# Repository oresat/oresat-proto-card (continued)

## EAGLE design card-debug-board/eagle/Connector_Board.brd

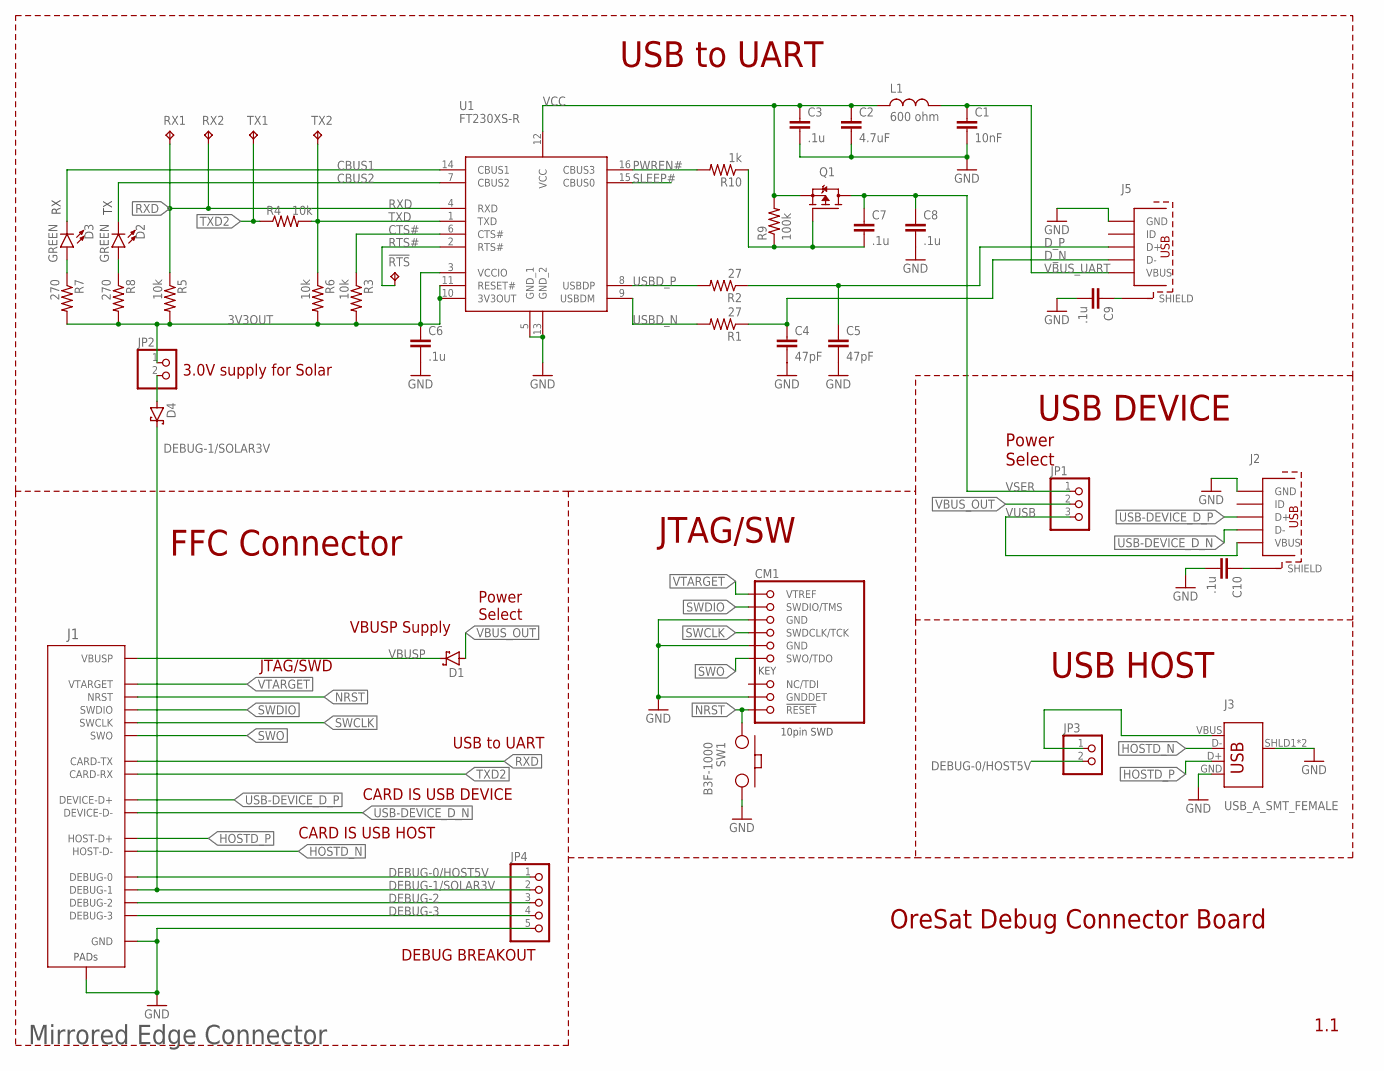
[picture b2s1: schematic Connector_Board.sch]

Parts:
!RTS: TEST-POINT-LARGE; 1X01
C1: 10nF; .0603-C-NOSILK; MANUFACTURER_PART_NUMBER 885382206002; DIGI-KEY_PART_NUMBER 732-13185-1-ND
C2: 4.7uF; .0603-C-NOSILK; MANUFACTURER_PART_NUMBER C1608X7S1A475K080AC; DIGI-KEY_PART_NUMBER 445-14258-1-ND
C3, C6, C7, C8, C9, C10: .1u; .0603-C-NOSILK; MANUFACTURER_PART_NUMBER 0603ZD104KAT2A; DIGI-KEY_PART_NUMBER 478-0603ZD104KAT2ACT-ND
C4, C5: 47pF; .0603-C-NOSILK; MANUFACTURER_PART_NUMBER 06033A470FAT2A; DIGI-KEY_PART_NUMBER 478-12679-1-ND
CM1: FTSH-105-XX-X-DV-K; CON10_2X5_DUK_FTSH; MANUFACTURER_PART_NUMBER FTSH-105-01-F-DV-K-TR; DIGI-KEY_PART_NUMBER SAM13160CT-ND
D1, D4: CDBU0520; DIOC1709X85N; MANUFACTURER_PART_NUMBER CDBU0520; DIGI-KEY_PART_NUMBER 641-1332-1-ND
D2, D3: GREEN; LED-0603; MANUFACTURER_PART_NUMBER 150060VS55040; DIGI-KEY_PART_NUMBER 732-12017-1-ND
J1: ORESAT-DEBUG-CONNECTOR-MIRRORED-ALL; TE_2-1734592-0; MANUFACTURER_PART_NUMBER 2-1734592-0; DIGI-KEY_PART_NUMBER A100287CT-ND
J2, J5: MICRO-USB-SOCKET; 629105136821; MANUFACTURER_PART_NUMBER 629105136821; DIGI-KEY_PART_NUMBER 732-3155-1-ND
J3: USB_A_SMT_FEMALE; USB-A-S-SILK-FEMALE; MANUFACTURER_PART_NUMBER PRT-09011; MOUSER_PART_NUMBER 474-PRT-09011
JP1: PINHD-1X3; 1X03; MANUFACTURER_PART_NUMBER 61300311121; DIGI-KEY_PART_NUMBER 732-5316-ND
JP2, JP3: PINHD-1X2; 1X02; MANUFACTURER_PART_NUMBER 61300211121; DIGI-KEY_PART_NUMBER 732-5315-ND
JP4: PINHD-1X5; 1X05; MANUFACTURER_PART_NUMBER 61300511121; DIGI-KEY_PART_NUMBER 732-5318-ND
L1: 600 ohm; .0805-A-NOSILK; MANUFACTURER_PART_NUMBER MI0805K601R-10; DIGI-KEY_PART_NUMBER 240-2390-1-ND
Q1: MOSFET-PCH-SOT23-6; SOT23-6; MANUFACTURER_PART_NUMBER SIL3407-TP; DIGI-KEY_PART_NUMBER SIL3407-TPMSCT-ND
R1, R2: 27; .0603-C-NOSILK; MANUFACTURER_PART_NUMBER CR0603-FX-27R0ELF; DIGI-KEY_PART_NUMBER CR0603-FX-27R0ELFCT-ND
R3, R4, R5, R6: 10k; .0603-C-NOSILK; MANUFACTURER_PART_NUMBER CR0603-FX-1002ELF; DIGI-KEY_PART_NUMBER CR0603-FX-1002ELFCT-ND
R7, R8: 270; .0603-C-NOSILK; MANUFACTURER_PART_NUMBER Panasonic Electronic Components; DIGI-KEY_PART_NUMBER P270HCT-ND
R9: 100k; .0603-C-NOSILK; MANUFACTURER_PART_NUMBER RMCF0603JG100K; DIGI-KEY_PART_NUMBER RMCF0603JG100KTR-ND
R10: 1k; .0603-C-NOSILK; MANUFACTURER_PART_NUMBER RC0603FR-071KL; DIGI-KEY_PART_NUMBER 311-1.00KHRCT-ND
RX1, RX2: TEST-POINT-LARGE; 1X01
SW1: B3F-1000; SW-MOM-OMRON-6X6X4.3; MANUFACTURER_PART_NUMBER B3F-1000; DIGI-KEY_PART_NUMBER SW400-ND
TX1, TX2: TEST-POINT-LARGE; 1X01
U1: FT230XS-R; SOP64P599X175-16N; DIGI-KEY_PART_NUMBER 768-1135-1-ND

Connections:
3V3OUT: C6.1, JP2.1, R3.2, R5.2, R6.2, R7.2, R8.2, U1.3 (VCCIO), U1.10 (3V3OUT), U1.11 (RESET#)
CBUS1: D3.C, U1.14 (CBUS1)
CBUS2: D2.C, U1.7 (CBUS2)
CTS#: R3.1, U1.6 (CTS#)
DEBUG-0/HOST5V: J1.4 (DEBUG-0), JP3.2, JP4.1
DEBUG-1/SOLAR3V: D4.1 (C), J1.3 (DEBUG-1), JP4.2
DEBUG-2: J1.2 (DEBUG-2), JP4.3
DEBUG-3: J1.1 (DEBUG-3), JP4.4
D_N: C4.1, J5.2 (D-), R1.1
D_P: C5.1, J5.3 (D+), R2.1
GND: C1.2, C2.2, C3.2, C4.2, C5.2, C6.2, C8.2, C9.2, C10.2, CM1.3 (GND), CM1.5 (GND), CM1.9 (GNDDET), J1.12 (GND), J1.15 (GND), J1.18 (GND), J1.PAD1 (PAD), J1.PAD2 (PAD), J2.5 (GND), J3.GND, J3.SHLD1 (SHIELD), J3.SHLD2 (SHIELD), J5.5 (GND), JP4.5, SW1.3 (2), SW1.4 (2), U1.5 (GND_1), U1.13 (GND_2)
HOSTD_N: J1.13 (HOST-D-), J3.D-
HOSTD_P: J1.14 (HOST-D+), J3.D+
unnamed: C9.1, J5.SHELL (SHIELD), J5.SHELL1 (SHIELD), J5.SHELL2 (SHIELD), J5.SHELL3 (SHIELD)
unnamed: J3.VBUS, JP3.1
unnamed: C7.2, Q1.3 (G), R9.1, R10.1
unnamed: D2.A, R8.1
unnamed: D3.A, R7.1
unnamed: C10.1, J2.SHELL (SHIELD), J2.SHELL1 (SHIELD), J2.SHELL2 (SHIELD), J2.SHELL3 (SHIELD)
unnamed: D4.2 (A), JP2.2
NRST: CM1.10 (!RESET), J1.11 (NRST), SW1.1, SW1.2 (1)
PWREN#: R10.2, U1.16 (CBUS3)
RTS#: !RTS.1, U1.2 (RTS#)
RXD: J1.8 (CARD-TX), R5.1, RX1.1, RX2.1, U1.4 (RXD)
SLEEP#: U1.15 (CBUS0)
SWCLK: CM1.4 (SWDCLK/TCK), J1.6 (SWCLK)
SWDIO: CM1.2 (SWDIO/TMS), J1.7 (SWDIO)
SWO: CM1.6 (SWO/TDO), J1.5 (SWO)
TXD: R4.2, R6.1, TX2.1, U1.1 (TXD)
TXD2: J1.9 (CARD-RX), R4.1, TX1.1
USB-DEVICE_D_N: J1.16 (DEVICE-D-), J2.2 (D-)
USB-DEVICE_D_P: J1.17 (DEVICE-D+), J2.3 (D+)
USBD_N: R1.2, U1.9 (USBDM)
USBD_P: R2.2, U1.8 (USBDP)
VBUSP: D1.1 (C), J1.19 (VBUSP), J1.20 (VBUSP)
VBUS_OUT: D1.2 (A), JP1.2
VBUS_UART: C1.1, J5.1 (VBUS), L1.2
VCC: C2.1, C3.1, L1.1, Q1.4 (S), R9.2, U1.12 (VCC)
VSER: C7.1, C8.1, JP1.1, Q1.1 (D), Q1.2 (D), Q1.5 (D), Q1.6 (D)
VTARGET: CM1.1 (VTREF), J1.10 (VTARGET)
VUSB: J2.1 (VBUS), JP1.3

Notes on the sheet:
USB to UART
FFC Connector
USB DEVICE
USB HOST
JTAG/SW
Power Select
OreSat Debug Connector Board
1.1
JTAG/SWD
CARD IS USB DEVICE
CARD IS USB HOST
DEBUG BREAKOUT
VBUSP Supply
Mirrored Edge Connector
3.0V supply for Solar

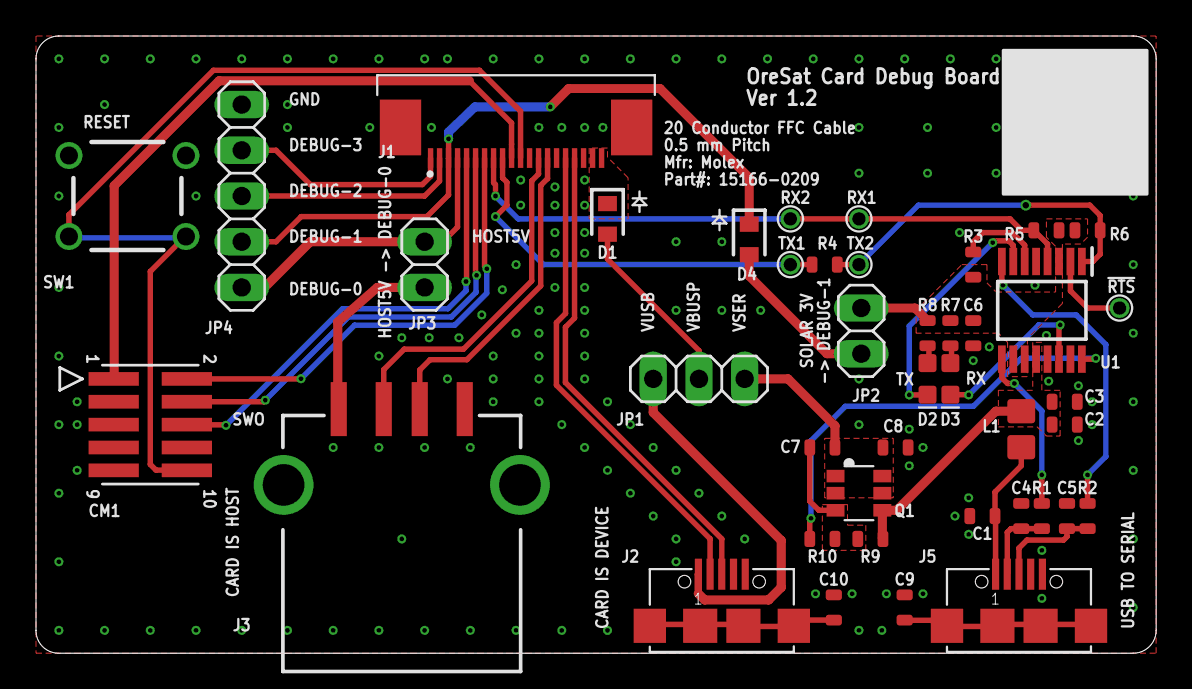
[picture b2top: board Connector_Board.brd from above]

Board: 2 copper layers, 62.2 x 34.3 mm, 42 parts (0 on the bottom side), 40 nets.

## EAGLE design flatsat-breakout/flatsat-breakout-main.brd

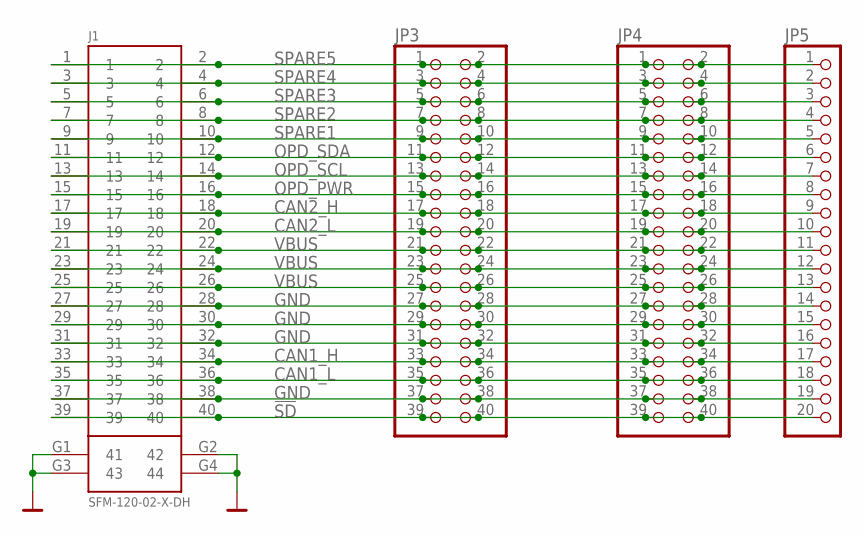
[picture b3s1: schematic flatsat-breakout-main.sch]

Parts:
J1: SFM-120-02-X-DH
JP3, JP4: PINHD-2X20; 2X20
JP5: PINHD-1X20; 1X20

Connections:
!SD: J1.39, J1.40, JP3.39, JP3.40, JP4.39, JP4.40, JP5.20
CAN1_H: J1.33, J1.34, JP3.33, JP3.34, JP4.33, JP4.34, JP5.17
CAN1_L: J1.35, J1.36, JP3.35, JP3.36, JP4.35, JP4.36, JP5.18
CAN2_H: J1.17, J1.18, JP3.17, JP3.18, JP4.17, JP4.18, JP5.9
CAN2_L: J1.19, J1.20, JP3.19, JP3.20, JP4.19, JP4.20, JP5.10
GND: J1.27, J1.28, J1.29, J1.30, J1.31, J1.32, J1.37, J1.38, J1.G1 (41), J1.G2 (42), J1.G3 (43), J1.G4 (44), JP3.27, JP3.28, JP3.29, JP3.30, JP3.31, JP3.32, JP3.37, JP3.38, JP4.27, JP4.28, JP4.29, JP4.30, JP4.31, JP4.32, JP4.37, JP4.38, JP5.14, JP5.15, JP5.16, JP5.19
OPD_PWR: J1.15, J1.16, JP3.15, JP3.16, JP4.15, JP4.16, JP5.8
OPD_SCL: J1.13, J1.14, JP3.13, JP3.14, JP4.13, JP4.14, JP5.7
OPD_SDA: J1.11, J1.12, JP3.11, JP3.12, JP4.11, JP4.12, JP5.6
SPARE1: J1.9, J1.10, JP3.9, JP3.10, JP4.9, JP4.10, JP5.5
SPARE2: J1.7, J1.8, JP3.7, JP3.8, JP4.7, JP4.8, JP5.4
SPARE3: J1.5, J1.6, JP3.5, JP3.6, JP4.5, JP4.6, JP5.3
SPARE4: J1.3, J1.4, JP3.3, JP3.4, JP4.3, JP4.4, JP5.2
SPARE5: J1.1, J1.2, JP3.1, JP3.2, JP4.1, JP4.2, JP5.1
VBUS: J1.21, J1.22, J1.23, J1.24, J1.25, J1.26, JP3.21, JP3.22, JP3.23, JP3.24, JP3.25, JP3.26, JP4.21, JP4.22, JP4.23, JP4.24, JP4.25, JP4.26, JP5.11, JP5.12, JP5.13

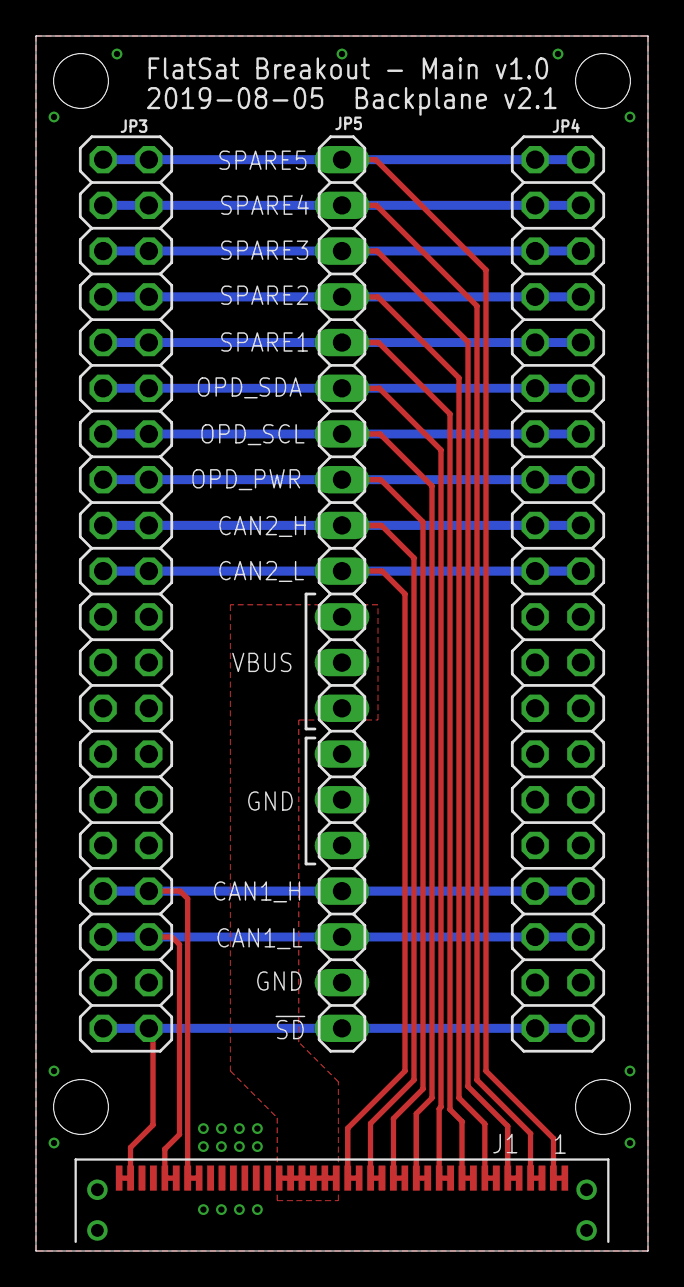
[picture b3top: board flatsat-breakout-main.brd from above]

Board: 2 copper layers, 34.0 x 67.5 mm, 8 parts (0 on the bottom side), 15 nets.

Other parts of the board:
H1, H3, H4, H5: STAND-OFFTIGHT; STAND-OFF-TIGHT

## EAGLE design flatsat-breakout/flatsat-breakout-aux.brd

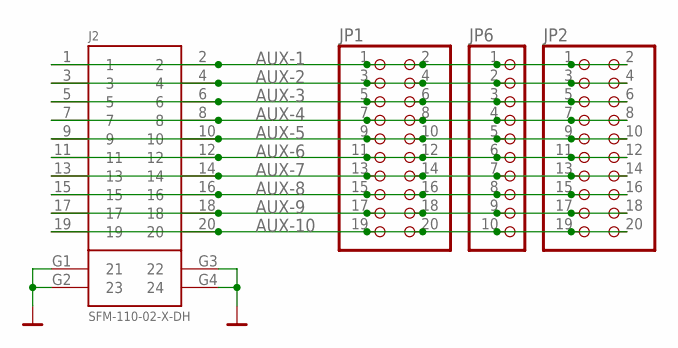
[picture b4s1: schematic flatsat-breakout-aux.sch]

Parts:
J2: SFM-110-02-X-DH
JP1, JP2: PINHD-2X10; 2X10
JP6: PINHD-1X10; 1X10

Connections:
AUX-1: J2.1, J2.2, JP1.1, JP1.2, JP2.1, JP2.2, JP6.1
AUX-2: J2.3, J2.4, JP1.3, JP1.4, JP2.3, JP2.4, JP6.2
AUX-3: J2.5, J2.6, JP1.5, JP1.6, JP2.5, JP2.6, JP6.3
AUX-4: J2.7, J2.8, JP1.7, JP1.8, JP2.7, JP2.8, JP6.4
AUX-5: J2.9, J2.10, JP1.9, JP1.10, JP2.9, JP2.10, JP6.5
AUX-6: J2.11, J2.12, JP1.11, JP1.12, JP2.11, JP2.12, JP6.6
AUX-7: J2.13, J2.14, JP1.13, JP1.14, JP2.13, JP2.14, JP6.7
AUX-8: J2.15, J2.16, JP1.15, JP1.16, JP2.15, JP2.16, JP6.8
AUX-9: J2.17, J2.18, JP1.17, JP1.18, JP2.17, JP2.18, JP6.9
AUX-10: J2.19, J2.20, JP1.19, JP1.20, JP2.19, JP2.20, JP6.10
GND: J2.G1 (21), J2.G2 (23), J2.G3 (22), J2.G4 (24)

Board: 2 copper layers, 9 parts (0 on the bottom side), 11 nets, no tracks yet.

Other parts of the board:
H1, H2, H3, H4, H5: STAND-OFFTIGHT; STAND-OFF-TIGHT

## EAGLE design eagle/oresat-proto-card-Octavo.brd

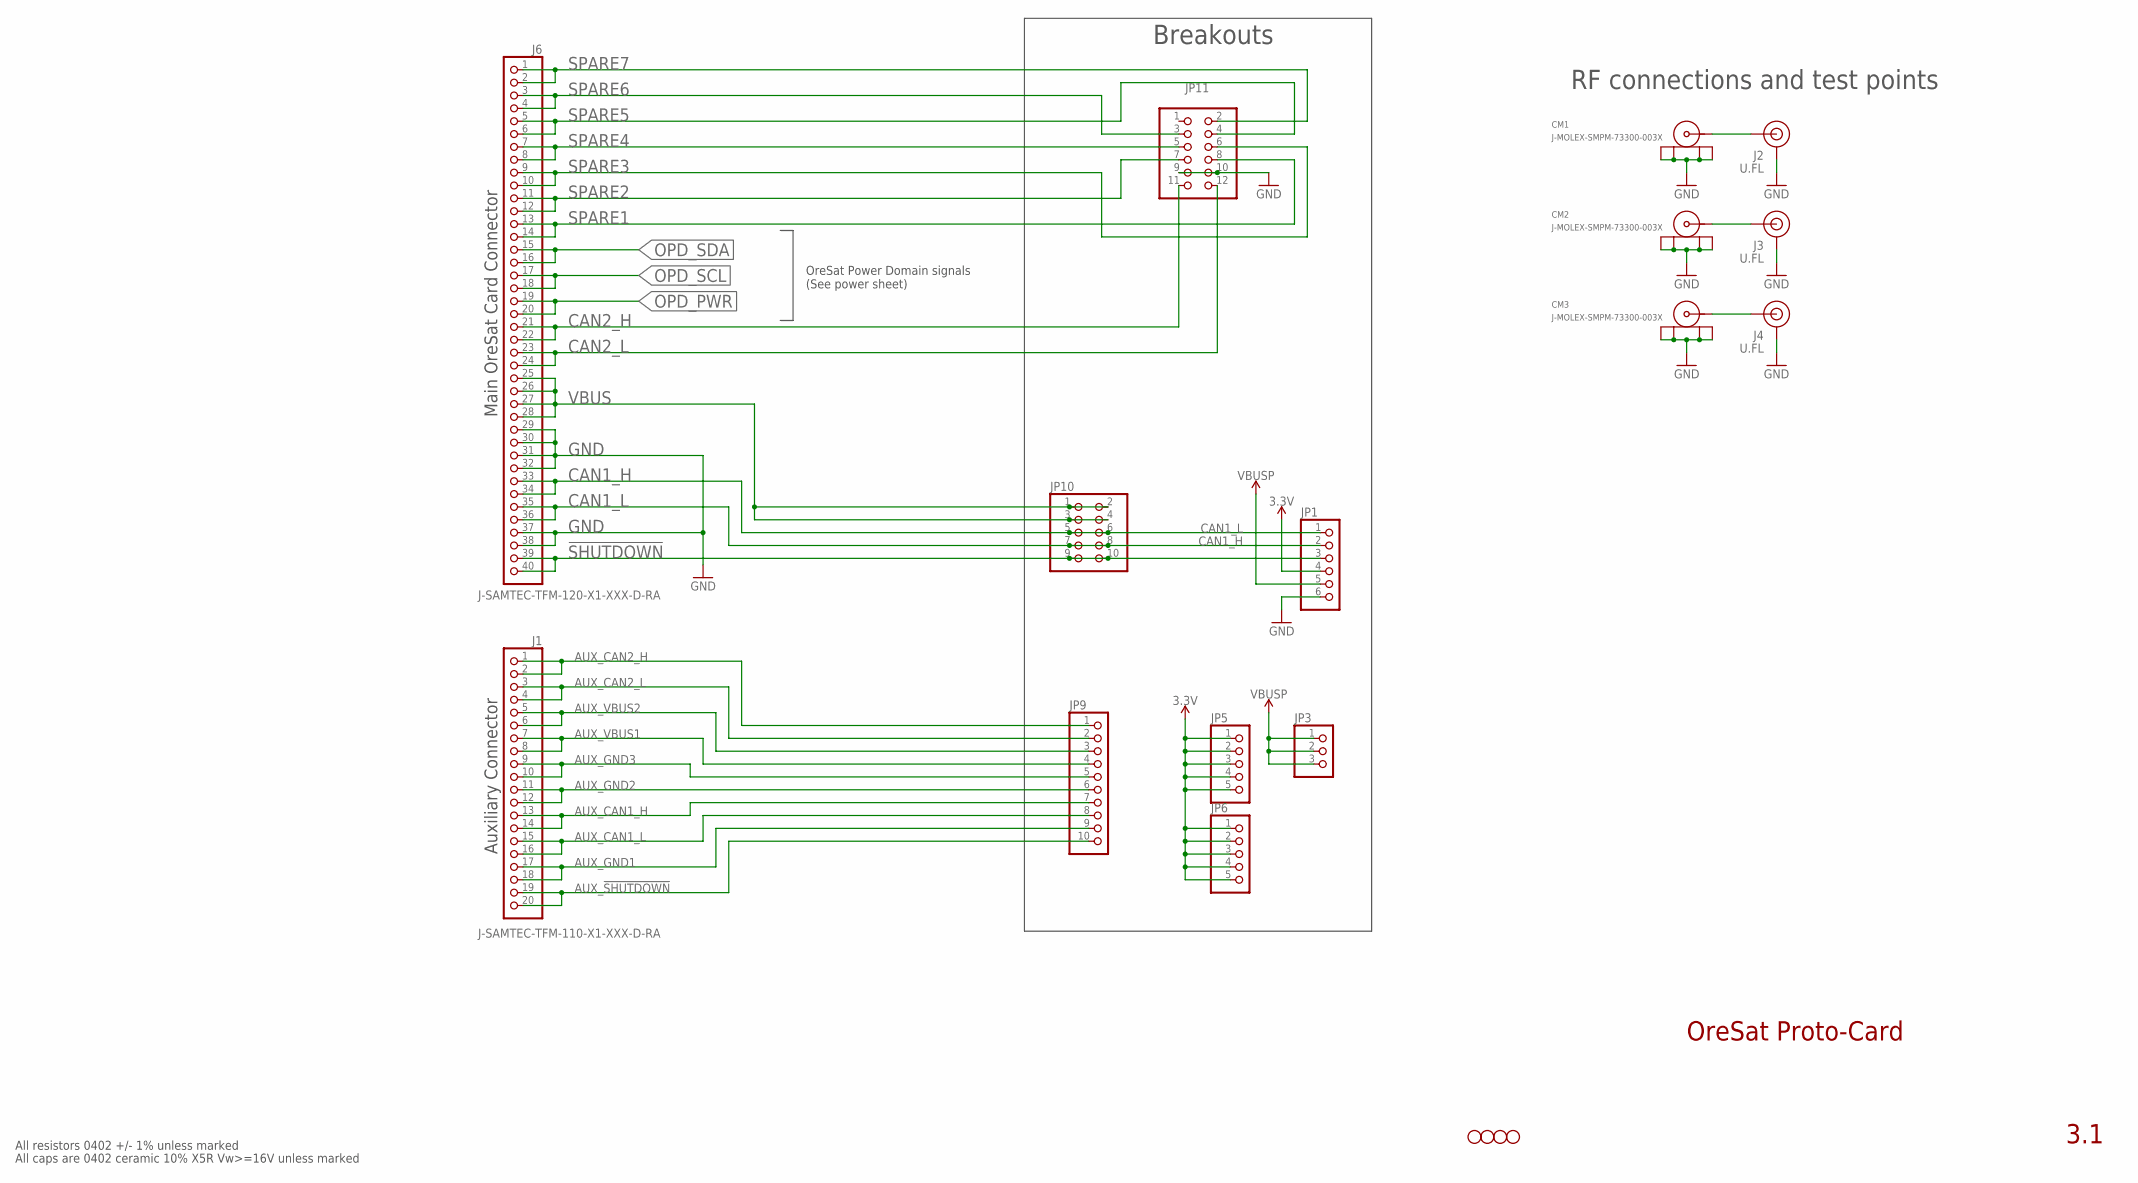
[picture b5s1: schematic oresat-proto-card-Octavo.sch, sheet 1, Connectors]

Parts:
CM1, CM2, CM3: J-MOLEX-SMPM-73300-003X; J-MOLEX-SMPM-073300-003X; MPN 73300-0020
H1, H2, H3, H4: STAND-OFFTIGHT; STAND-OFF-TIGHT
J1: J-SAMTEC-TFM-110-X1-XXX-D-RA; MPN TFM-110-01-L-D-RA
J2, J3, J4: U.FL
J6: J-SAMTEC-TFM-120-X1-XXX-D-RA; MPN TFM-120-01-L-D-RA
JP1: PINHD-1X6; 1X06
JP3: PINHD-1X3; 1X03
JP5, JP6: PINHD-1X5; 1X05
JP9: PINHD-1X10; 1X10
JP10: PINHD-2X5; 2X05
JP11: PINHD-2X6; 2X06

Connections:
3.3V: JP1.4, JP5.1, JP5.2, JP5.3, JP5.4, JP5.5, JP6.1, JP6.2, JP6.3, JP6.4, JP6.5; also elsewhere on the board
!SHUTDOWN: J6.39, J6.40, JP1.3, JP10.9, JP10.10
AUX_!SHUTDOWN: J1.19, J1.20, JP9.10
AUX_CAN1_H: J1.13, J1.14, JP9.7
AUX_CAN1_L: J1.15, J1.16, JP9.8
AUX_CAN2_H: J1.1, J1.2, JP9.1
AUX_CAN2_L: J1.3, J1.4, JP9.2
AUX_GND1: J1.17, J1.18, JP9.9
AUX_GND2: J1.11, J1.12, JP9.6
AUX_GND3: J1.9, J1.10, JP9.5
AUX_VBUS1: J1.7, J1.8, JP9.4
AUX_VBUS2: J1.5, J1.6, JP9.3
CAN1_H: J6.33, J6.34, JP1.1, JP10.5, JP10.6; also elsewhere on the board
CAN1_L: J6.35, J6.36, JP1.2, JP10.7, JP10.8; also elsewhere on the board
CAN2_H: J6.21, J6.22, JP11.11
CAN2_L: J6.23, J6.24, JP11.12
GND: CM1.P$1 (SHIELD3), CM1.P$2 (SHIELD2), CM1.P$3 (SHIELD1), CM1.P$4 (SHIELD), CM2.P$1 (SHIELD3), CM2.P$2 (SHIELD2), CM2.P$3 (SHIELD1), CM2.P$4 (SHIELD), CM3.P$1 (SHIELD3), CM3.P$2 (SHIELD2), CM3.P$3 (SHIELD1), CM3.P$4 (SHIELD), J2.1 (GND), J2.2 (GND), J3.1 (GND), J3.2 (GND), J4.1 (GND), J4.2 (GND), J6.29, J6.30, J6.31, J6.32, J6.37, J6.38, JP1.6, JP11.9, JP11.10; also elsewhere on the board
unnamed: CM3.RF (CENTER), J4.FEED (SIGNAL)
OPD_PWR: J6.19, J6.20; also elsewhere on the board
OPD_SCL: J6.17, J6.18; also elsewhere on the board
OPD_SDA: J6.15, J6.16; also elsewhere on the board
RF1: CM1.RF (CENTER), J2.FEED (SIGNAL)
RF2: CM2.RF (CENTER), J3.FEED (SIGNAL)
SPARE1: J6.13, J6.14, JP11.8
SPARE2: J6.11, J6.12, JP11.7
SPARE3: J6.9, J6.10, JP11.6
SPARE4: J6.7, J6.8, JP11.5
SPARE5: J6.5, J6.6, JP11.4
SPARE6: J6.3, J6.4, JP11.3
SPARE7: J6.1, J6.2, JP11.2
VBUS: J6.25, J6.26, J6.27, J6.28, JP10.1, JP10.2, JP10.3, JP10.4; also elsewhere on the board
VBUSP: JP1.5, JP3.1, JP3.2, JP3.3; also elsewhere on the board

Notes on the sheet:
OreSat Proto-Card
3.1
All resistors 0402 +/- 1% unless marked
All caps are 0402 ceramic 10% X5R Vw>=16V unless marked
Auxiliary Connector
Main OreSat Card Connector
RF connections and test points
Breakouts
OreSat Power Domain signals (See power sheet)

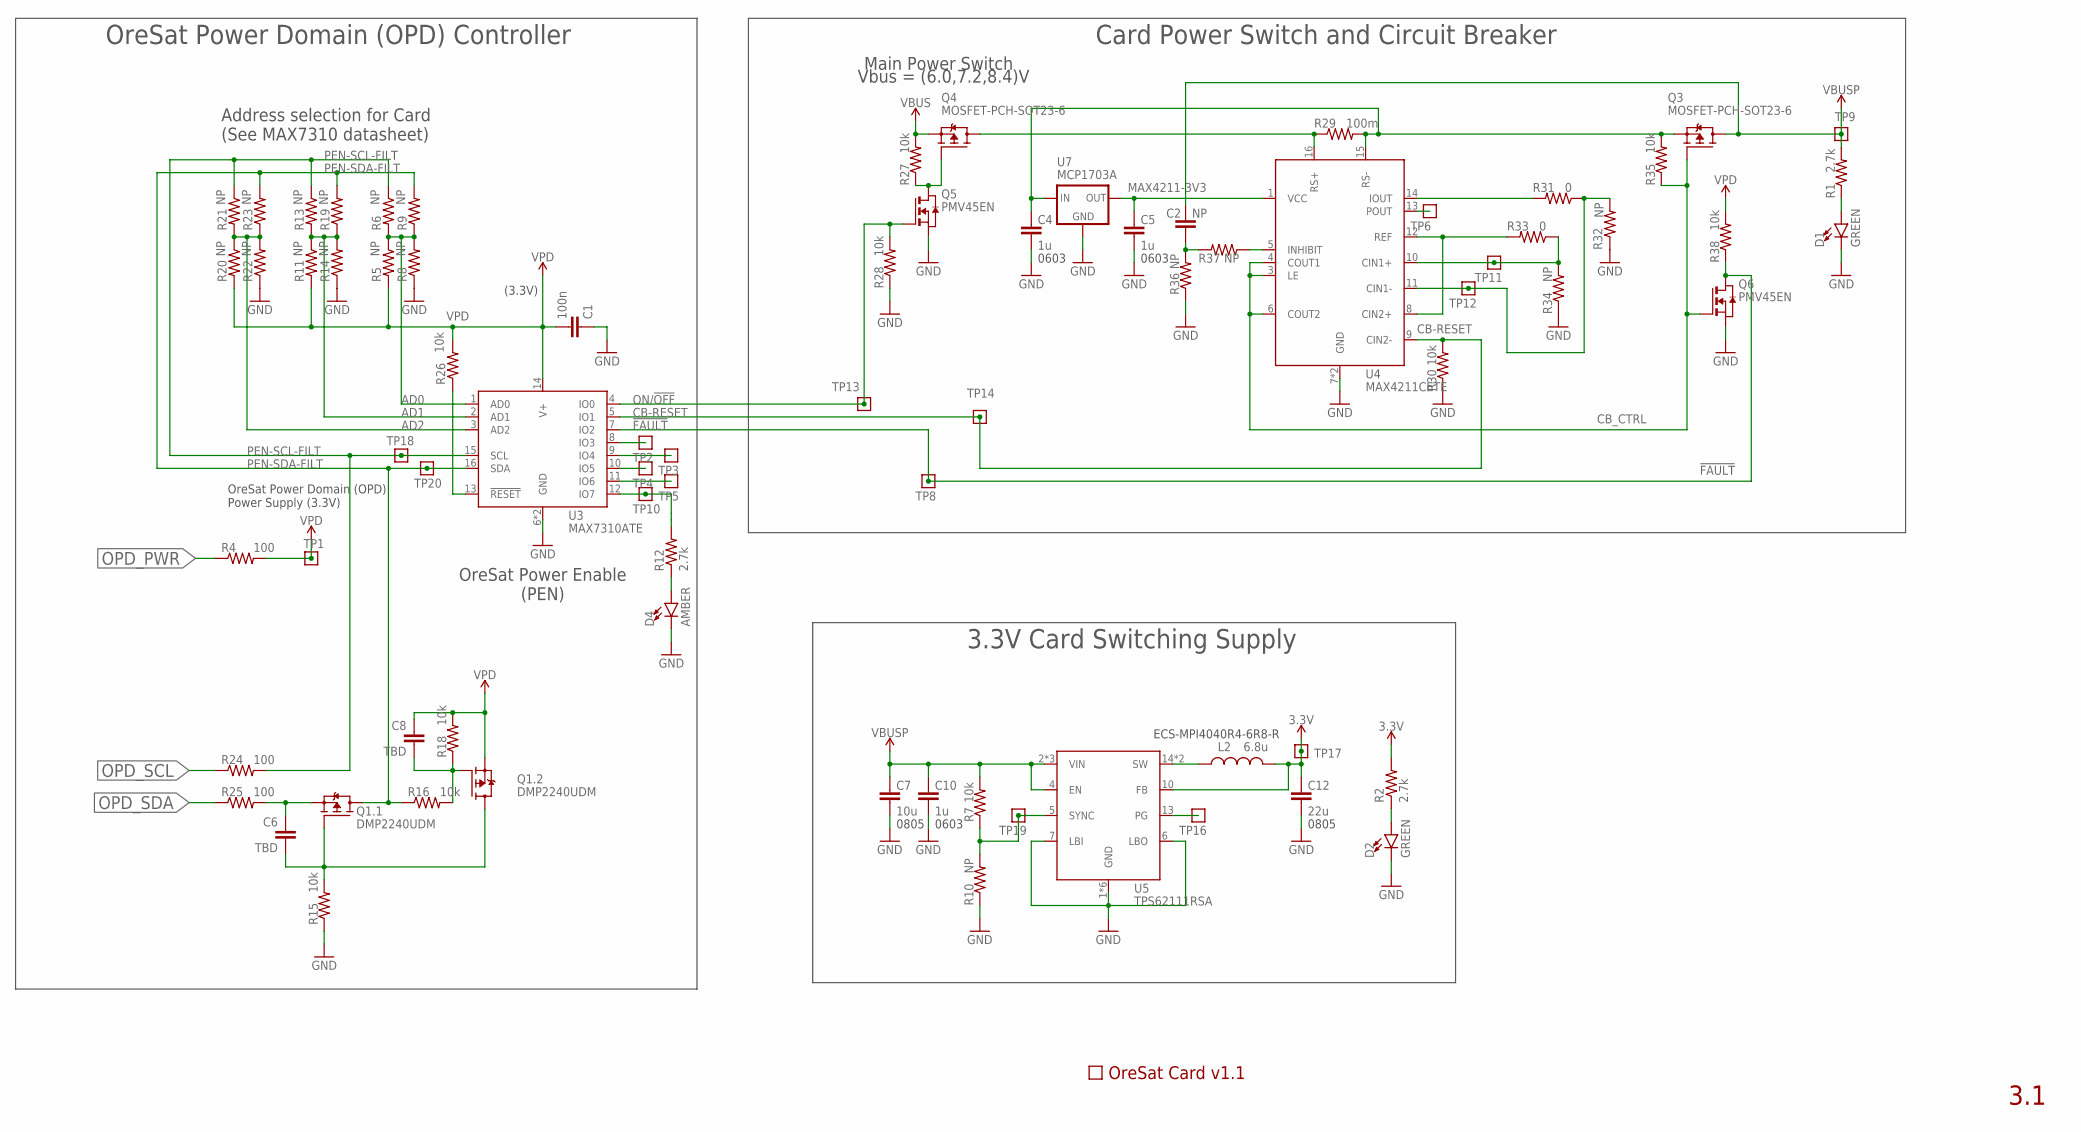
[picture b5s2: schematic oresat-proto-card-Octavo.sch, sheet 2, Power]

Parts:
C1: 100n; .0402-B-NOSILK; MPN CL05B104KO5NNNC
C2: NP; .0402-B-NOSILK; MPN CL05B104KO5NNNC
C4, C5, C10: 1u; .0603-B-NOSILK; MPN CL05B104KO5NNNC
C6, C8: TBD; .0402-B-NOSILK; MPN CL05B104KO5NNNC
C7: 10u; .0805-B-NOSILK
C12: 22u; .0805-B-NOSILK
D1, D2: GREEN; LED-0603
D4: AMBER; LED-0603
L2: 6.8u; ECS-MPI4040; MPN ECS-MPI4040R4-6R8-R
Q1: DMP2240UDM; SOT23-6; MPN DMP2240UDM
Q3, Q4: MOSFET-PCH-SOT23-6; SOT23-6; MPN DMP3050LVT-7
Q5, Q6: PMV45EN; SOT23
R1, R2, R12: 2.7k; .0402-B-NOSILK; MPN RC1005F6653CS
R4, R24, R25: 100; .0402-B-NOSILK; MPN RC1005F6653CS
R5, R6, R8, R9, R10, R11, R13, R14, R19, R20, R21, R22, R23, R32, R34, R36, R37: NP; .0402-B-NOSILK; MPN RC1005F6653CS
R7, R15, R16, R18, R26, R27, R28, R30, R35, R38: 10k; .0402-B-NOSILK; MPN RC1005F6653CS
R29: 100m; R1206
R31, R33: 0; .0402-B-NOSILK; MPN RC1005F6653CS
TP1, TP2, TP3, TP4, TP5, TP6, TP8, TP9, TP10, TP11, TP12, TP13, TP14, TP16, TP17, TP18, TP19, TP20: TEST-POINT; 2MM-TEST-POINT
U3: MAX7310ATE; QFN65P400X400X80-17T210; MPN MAX7310ATE
U4: MAX4211CETE; QFN65P400X400X80-17T210; MPN MAX4211CETE
U5: TPS62111RSA; S-PVQFN-16; MPN TPS62111RSA
U7: MCP1703A; SOT23; MPN MCP1703AT-3302E/CB
U$1: ORESAT-CARD-V1.1-3XRF

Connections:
3.3V: C12.1, L2.2, R2.2, TP17.1, U5.10 (FB); also elsewhere on the board
!FAULT: Q6.3 (D), R38.1, TP8.1, U3.7 (IO2)
AD0: R5.1, R6.2, R8.2, R9.1, U3.1 (AD0)
AD1: R11.1, R13.2, R14.2, R19.1, U3.2 (AD1)
AD2: R20.1, R21.2, R22.2, R23.1, U3.3 (AD2)
CB-RESET: R30.2, TP14.1, U3.5 (IO1), U4.9 (CIN2-)
CB_CTRL: Q3.3 (G), Q6.1 (G), R35.1, U4.3 (LE), U4.4 (COUT1), U4.6 (COUT2)
GND: C1.1, C4.2, C5.2, C7.2, C10.2, C12.2, D1.C, D2.C, D4.C, Q5.2 (S), Q6.2 (S), R8.1, R10.1, R14.1, R15.1, R22.1, R28.1, R30.1, R32.1, R34.1, R36.1, U3.6 (GND), U3.EPAD (GND), U4.7 (GND), U4.EPAD (GND), U5.1 (GND), U5.6 (LBO), U5.7 (LBI), U5.9 (GND), U5.11 (GND), U5.12 (GND), U5.16 (GND), U5.PAD (GND), U7.1 (GND); also elsewhere on the board
MAX4211-3V3: C5.1, U4.1 (VCC), U7.2 (OUT)
unnamed: D1.A, R1.1
unnamed: D2.A, R2.1
unnamed: C4.1, Q3.4 (S), R29.2, R35.2, U4.15 (RS-), U7.3 (IN)
unnamed: TP2.1, U3.8 (IO3)
unnamed: TP3.1, U3.9 (IO4)
unnamed: TP4.1, U3.10 (IO5)
unnamed: TP5.1, U3.11 (IO6)
unnamed: R12.2, TP10.1, U3.12 (IO7)
unnamed: D4.A, R12.1
unnamed: C6.1, Q1.5 (S), R25.2
unnamed: C6.2, Q1.1 (G), Q1.4 (D), R15.2
unnamed: C8.2, Q1.3 (G), R16.2, R18.1
unnamed: R26.1, U3.13 (!RESET)
unnamed: Q4.3 (G), Q5.3 (D), R27.1
unnamed: Q4.1 (D), Q4.2 (D), Q4.5 (D), Q4.6 (D), R29.1, U4.16 (RS+)
unnamed: R31.1, R32.2, TP12.1, U4.11 (CIN1-)
unnamed: R33.1, R34.2, TP11.1, U4.10 (CIN1+)
unnamed: R31.2, U4.14 (IOUT)
unnamed: R33.2, U4.8 (CIN2+), U4.12 (REF)
unnamed: TP6.1, U4.13 (POUT)
unnamed: C2.1, R36.2, R37.2
unnamed: R37.1, U4.5 (INHIBIT)
ON/!OFF: Q5.1 (G), R28.2, TP13.1, U3.4 (IO0)
OPD_PWR: R4.1; also elsewhere on the board
OPD_SCL: R24.1; also elsewhere on the board
OPD_SDA: R25.1; also elsewhere on the board
PEN-SCL-FILT: R6.1, R13.1, R21.1, R24.2, TP18.1, U3.15 (SCL)
PEN-SDA-FILT: Q1.6 (D), R9.2, R16.1, R19.2, R23.2, TP20.1, U3.16 (SDA)
TPS62111-PG: TP16.1, U5.13 (PG)
TPS62111-SYNC: R7.1, R10.2, TP19.1, U5.5 (SYNC)
TPS62111_SW: L2.1, U5.14 (SW), U5.15 (SW)
VBUS: Q4.4 (S), R27.2; also elsewhere on the board
VBUSP: C2.2, C7.1, C10.1, Q3.1 (D), Q3.2 (D), Q3.5 (D), Q3.6 (D), R1.2, R7.2, TP9.1, U5.2 (VIN), U5.3 (VIN), U5.4 (EN), U5.8 (VIN); also elsewhere on the board
VPD: C1.2, C8.1, Q1.2 (S), R4.2, R5.2, R11.2, R18.2, R20.2, R26.2, R38.2, TP1.1, U3.14 (V+)

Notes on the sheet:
Main Power Switch
OreSat Power Enable (PEN)
Address selection for Card (See MAX7310 datasheet)
(3.3V)
0805
0603
ECS-MPI4040R4-6R8-R
Vbus = (6.0,7.2,8.4)V
OreSat Power Domain (OPD) Power Supply (3.3V)
OreSat Power Domain (OPD) Controller
3.3V Card Switching Supply
Card Power Switch and Circuit Breaker
3.1
